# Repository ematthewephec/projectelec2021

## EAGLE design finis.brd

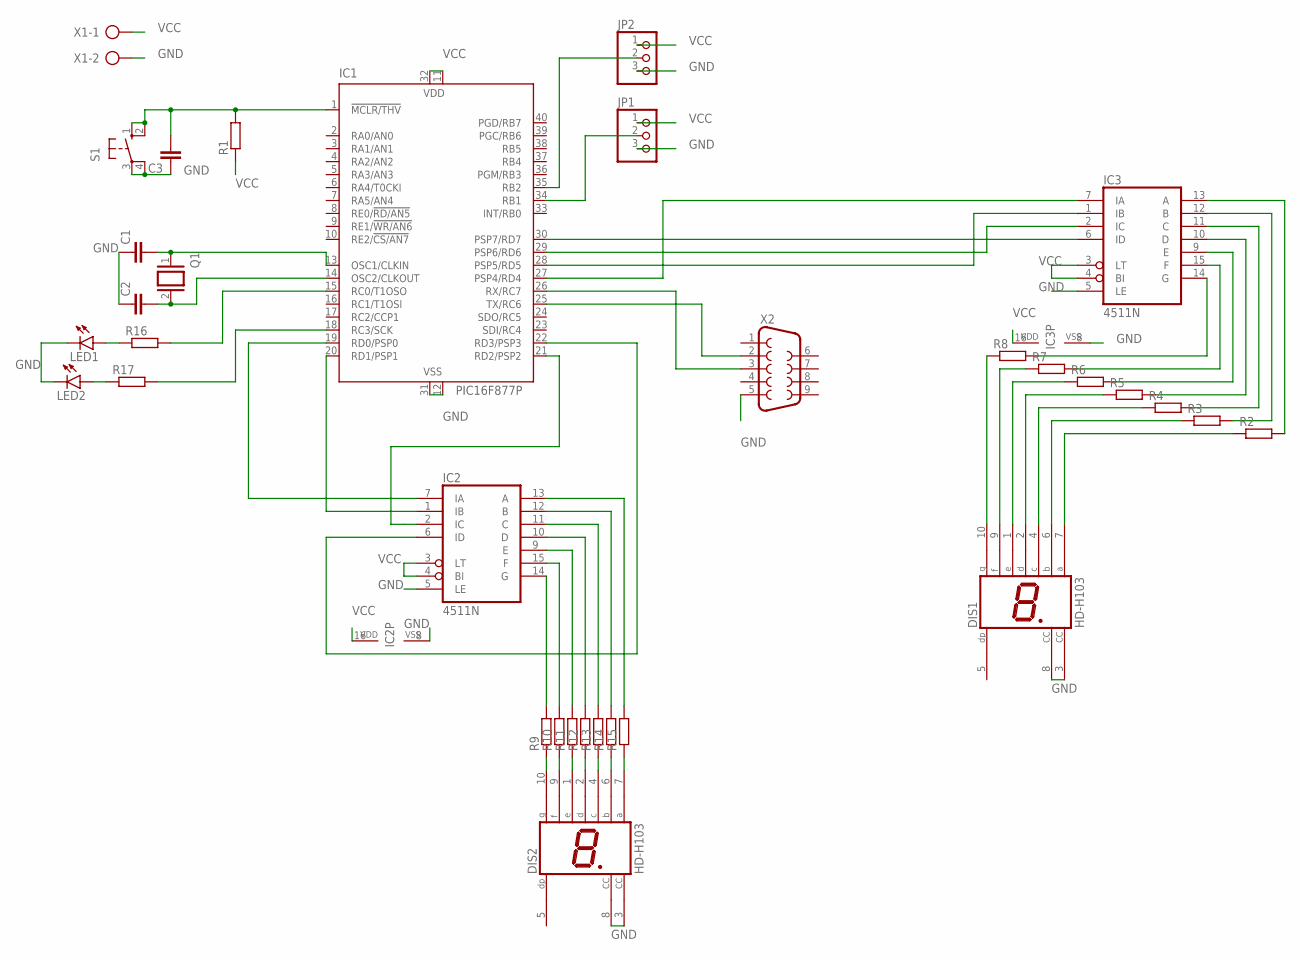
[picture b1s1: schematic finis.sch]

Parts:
C1, C2, C3: C-EU025-025X050; C025-025X050
DIS1, DIS2: HD-H103; HDSP-M
IC1: PIC16F877P; DIL40
IC2, IC3: 4511N; DIL16
JP1, JP2: PINHD-1X3; 1X03
LED1, LED2: LED5MM
Q1: XTAL/S; QS
R1, R2, R3, R4, R5, R6, R7, R8, R9, R10, R11, R12, R13, R14, R15, R16, R17: R-EU_0207/10; 0207/10
S1: 10-XX; B3F-10XX
X1: AK300/2
X2: F09H

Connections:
GND: C1.1, C2.1, C3.1, DIS1.3 (CC), DIS1.8 (CC), DIS2.3 (CC), DIS2.8 (CC), IC1.12 (VSS), IC1.31 (VSS), IC2.5 (LE), IC2.8 (VSS), IC3.5 (LE), IC3.8 (VSS), JP1.3, JP2.3, LED1.K (C), LED2.K (C), S1.3, S1.4 (P1), X1.2, X2.5
unnamed: C1.2, IC1.13 (OSC1/CLKIN), Q1.1
unnamed: C2.2, IC1.14 (OSC2/CLKOUT), Q1.2
unnamed: C3.2, IC1.1 (!MCLR/THV), R1.2, S1.1 (S), S1.2 (S1)
unnamed: IC1.19 (RD0/PSP0), IC2.7 (IA)
unnamed: IC1.20 (RD1/PSP1), IC2.1 (IB)
unnamed: IC1.22 (RD3/PSP3), IC2.6 (ID)
unnamed: IC1.27 (PSP4/RD4), IC3.7 (IA)
unnamed: IC1.28 (PSP5/RD5), IC3.1 (IB)
unnamed: IC1.29 (PSP6/RD6), IC3.2 (IC)
unnamed: IC1.30 (PSP7/RD7), IC3.6 (ID)
unnamed: IC3.13 (A), R2.2
unnamed: IC3.12 (B), R3.2
unnamed: IC3.11 (C), R4.2
unnamed: IC3.10 (D), R5.2
unnamed: IC3.9 (E), R6.2
unnamed: DIS1.9 (F), R7.1
unnamed: DIS1.10 (G), R8.1
unnamed: DIS1.7 (A), R2.1
unnamed: DIS1.6 (B), R3.1
unnamed: DIS1.4 (C), R4.1
unnamed: DIS1.2 (D), R5.1
unnamed: DIS1.1 (E), R6.1
unnamed: IC3.15 (F), R7.2
unnamed: IC3.14 (G), R8.2
unnamed: DIS2.10 (G), R9.1
unnamed: DIS2.9 (F), R10.1
unnamed: DIS2.1 (E), R11.1
unnamed: DIS2.2 (D), R12.1
unnamed: DIS2.4 (C), R13.1
unnamed: DIS2.6 (B), R14.1
unnamed: DIS2.7 (A), R15.1
unnamed: IC2.14 (G), R9.2
unnamed: IC2.15 (F), R10.2
unnamed: IC2.9 (E), R11.2
unnamed: IC2.10 (D), R12.2
unnamed: IC2.11 (C), R13.2
unnamed: IC2.12 (B), R14.2
unnamed: IC2.13 (A), R15.2
unnamed: LED1.A, R16.1
unnamed: LED2.A, R17.1
unnamed: IC1.18 (RC3/SCK), R17.2
unnamed: IC1.15 (RC0/T1OSO), R16.2
unnamed: IC1.25 (TX/RC6), X2.2
unnamed: IC1.26 (RX/RC7), X2.3
unnamed: IC1.35 (RB2), JP2.2
unnamed: IC1.34 (RB1), JP1.2
VCC: IC1.11 (VDD), IC1.32 (VDD), IC2.3 (LT), IC2.4 (BI), IC2.16 (VDD), IC3.3 (LT), IC3.4 (BI), IC3.16 (VDD), JP1.1, JP2.1, R1.1, X1.1

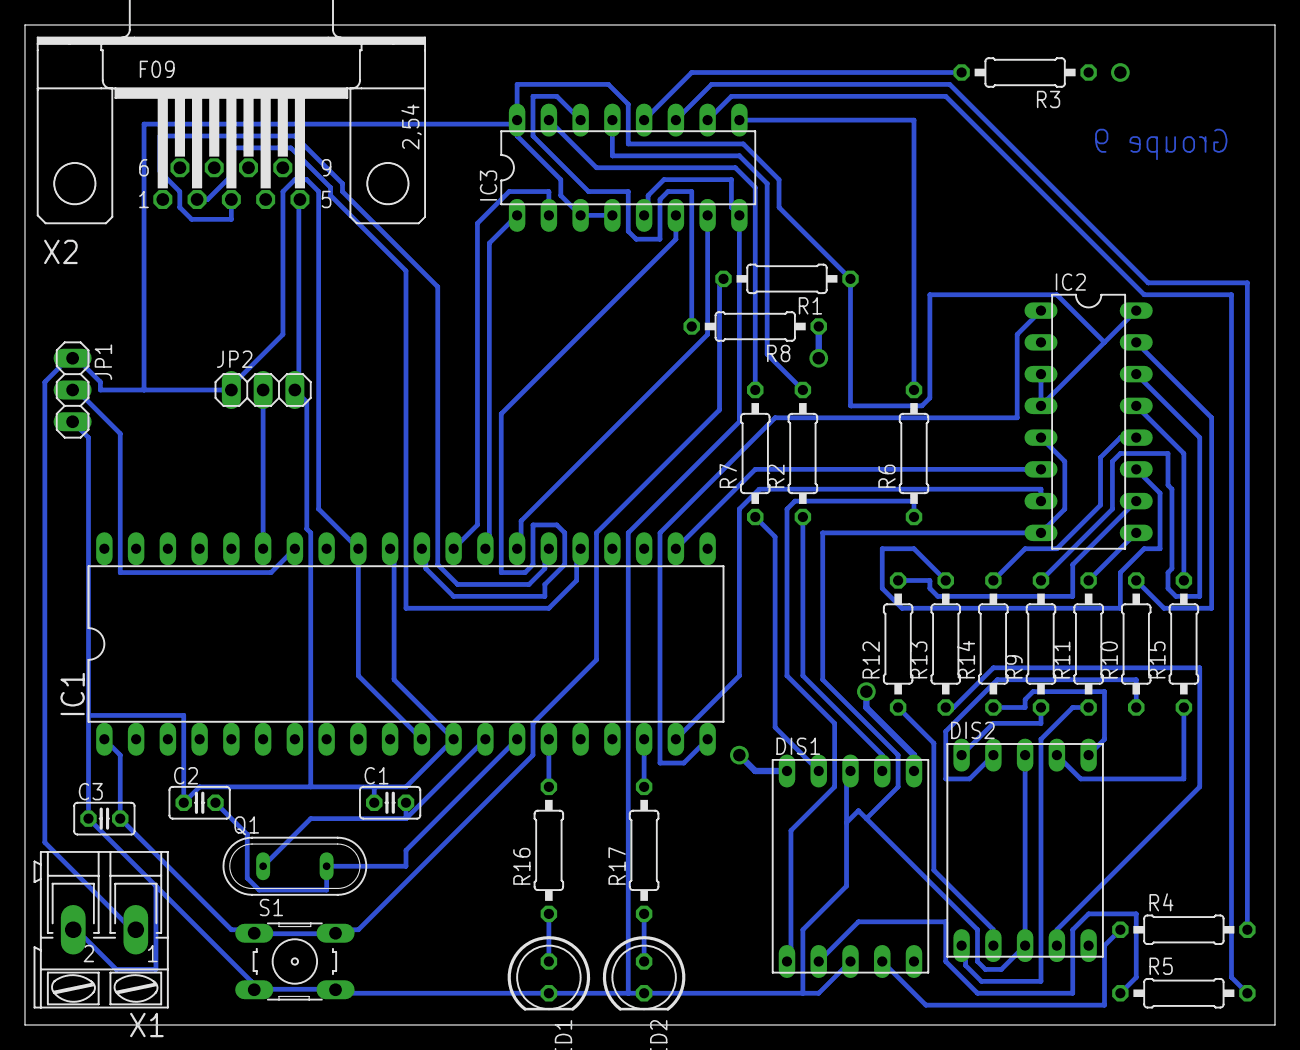
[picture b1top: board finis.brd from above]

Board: 2 copper layers, 100.0 x 80.0 mm, 33 parts (0 on the bottom side), 48 nets.

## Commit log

2021-05-16 ajouts des fichiers
2021-05-16 ajouts des fichiers des pcb
2021-05-17 rapport
